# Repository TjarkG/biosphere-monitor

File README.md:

# Getting started with the Biosphere monitor command line tool

Get the repository and all its dependencies by running
`/bin/bash -c "$(curl -fsSL  https://raw.githubusercontent.com/TjarkG/biosphere-monitor/main/Shell/install.sh)"`

The Command line interface is started with `./biosphere`,
followed by a Port number (e.g. `/dev/ttyUSB0`) and optional arguments,
which can occur in any order, listed below:

* -h    show this help message
* -r    show current reading in Command line Output
* -rm   current output in machine-readable formate
* -s    show all saved readings. use pipes to save to a file
* -sc   same as -s, but with progress Updates on the Terminal. Use it to see the progress while piping
* -f    synchronize time
* -i    set measurement intervall in s, use -i? to get current intervall
* -t    run self test
* -ct   set current ambient Temperature(°C), used for Offset Calibration
* -delete delete Flash
* -gh   get current ADC reading of external input
* -ltn  set light on time, use -ltn? to get current setting
* -ltf  set light off time, use -ltf? to get current setting
* -lt   set light threshold, 0 for no threshold, use -lt? to get current setting

After cloning, generate makefiles with cmake:
```
mkdir cmake-build-debug
cd cmake-build-debug
cmake ..
```
and Compile the different programs:

* Command Line Tool: `make biosphere && ./biosphere /dev/ttyUSB0 -r`
* Graphical Configurator: `make bioGui`
* Microcontroller: `make Microcontroller.elf`

Check your data for Gaps with
`gawk -f Shell/gaps.awk gap=60 Documentation/Sample_Output.csv`
(gap is the intervall in s, each following argument is a Path to File to be checkt)

And convert it to an Excel Spreadsheet with
`soffice --convert-to xlsx --outdir ~/Dokumente/VS_Code/biosphere-monitor/Documentation Documentation/Sample_Output.csv --infilter=CSV:44,34,UTF8,true,3/10/4/10`

Complete Documentation (in German) can be found in /Documentation/Manual.pdf

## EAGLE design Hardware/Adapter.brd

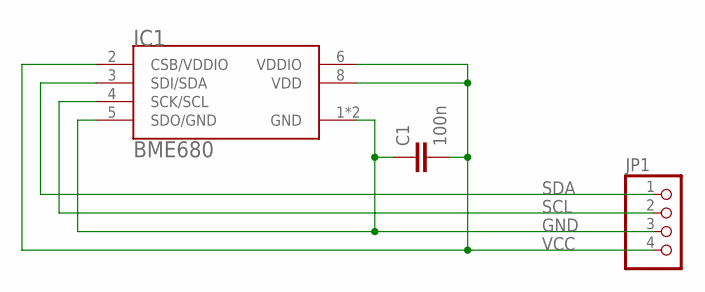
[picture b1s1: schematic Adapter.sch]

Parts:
C1: 100n; C0805
IC1: BME680; LGA8
JP1: PINHD-1X4; 1X04

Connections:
GND: C1.1, IC1.1 (GND), IC1.5 (SDO/GND), IC1.7 (GND), JP1.3
SCL: IC1.4 (SCK/SCL), JP1.2
SDA: IC1.3 (SDI/SDA), JP1.1
VCC: C1.2, IC1.2 (CSB/VDDIO), IC1.6 (VDDIO), IC1.8 (VDD), JP1.4

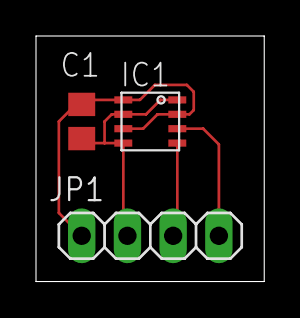
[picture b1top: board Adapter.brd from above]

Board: 2 copper layers, 12.7 x 13.6 mm, 3 parts (0 on the bottom side), 4 nets.

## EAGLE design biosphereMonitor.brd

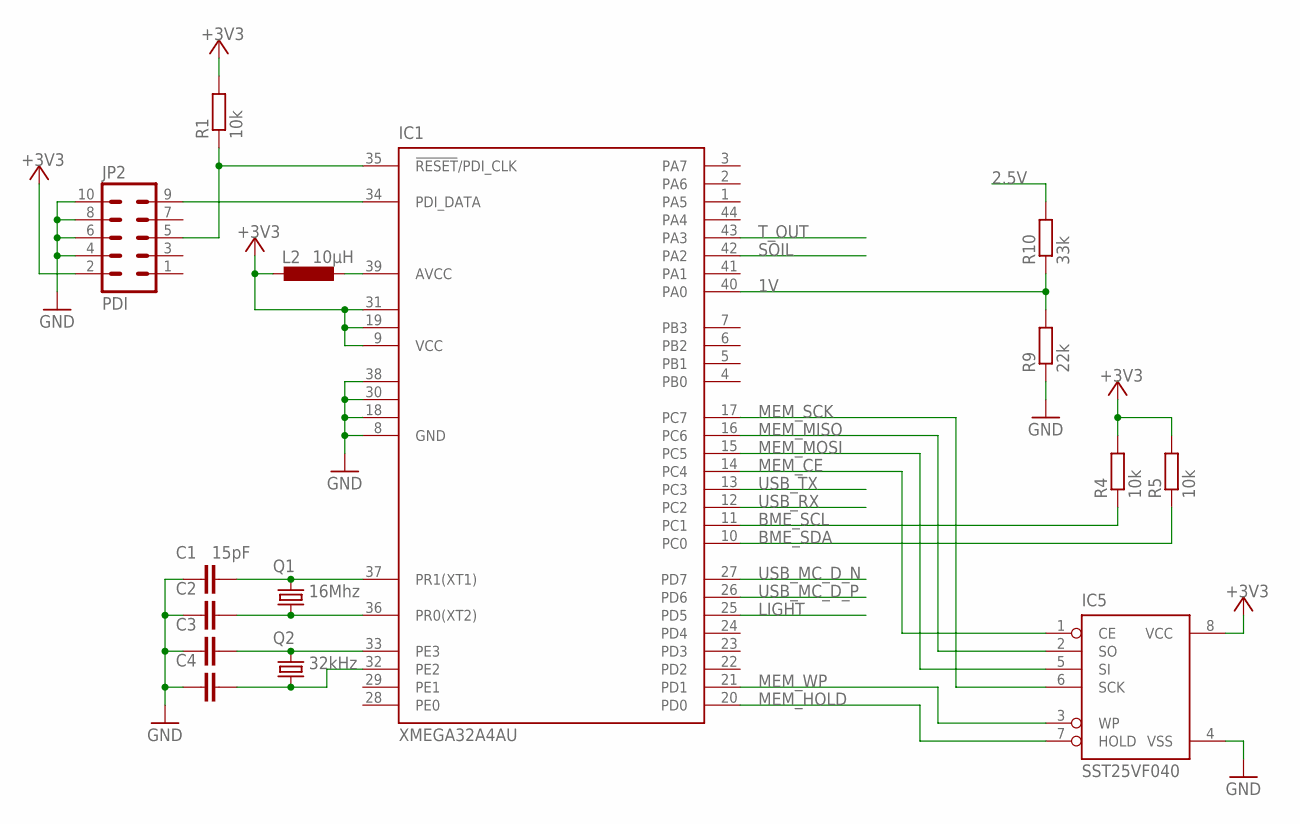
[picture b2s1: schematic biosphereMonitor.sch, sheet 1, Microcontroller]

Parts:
C1, C2, C3, C4: 15pF; C0805
IC1: XMEGA32A4AU; TQFP44
IC5: SST25VF040; SO08-208
JP2: PDI; ML10L
L2: 10µH; L2012C
Q1: 16Mhz; SM49
Q2: 32kHz; MS1V
R1, R4, R5: 10k; R0805
R9: 22k; R0805
R10: 33k; R0805

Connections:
1V: IC1.40 (PA0), R9.2, R10.1
2.5V: R10.2; also elsewhere on the board
+3V3: IC1.9 (VCC), IC1.19 (VCC1), IC1.31 (VCC2), IC5.8 (VCC), JP2.2, L2.1, R1.2, R4.2, R5.2; also elsewhere on the board
AVCC: IC1.39 (AVCC), L2.2
BME_SCL: IC1.11 (PC1), R4.1; also elsewhere on the board
BME_SDA: IC1.10 (PC0), R5.1; also elsewhere on the board
GND: C1.1, C2.1, C3.1, C4.1, IC1.8 (GND), IC1.18 (GND1), IC1.30 (GND2), IC1.38 (GND3), IC5.4 (VSS), JP2.4, JP2.6, JP2.8, JP2.10, R9.1; also elsewhere on the board
LIGHT: IC1.25 (PD5); also elsewhere on the board
MEM_CE: IC1.14 (PC4), IC5.1 (CE)
MEM_HOLD: IC1.20 (PD0), IC5.7 (HOLD)
MEM_MISO: IC1.16 (PC6), IC5.2 (SO)
MEM_MOSI: IC1.15 (PC5), IC5.5 (SI)
MEM_SCK: IC1.17 (PC7), IC5.6 (SCK)
MEM_WP: IC1.21 (PD1), IC5.3 (WP)
unnamed: IC1.35 (!RESET!/PDI_CLK), JP2.5, R1.1
unnamed: IC1.34 (PDI_DATA), JP2.9
unnamed: C1.2, IC1.37 (PR1(XT1)), Q1.2
unnamed: C2.2, IC1.36 (PR0(XT2)), Q1.1
unnamed: C3.2, IC1.33 (PE3), Q2.Q1 (1)
unnamed: C4.2, IC1.32 (PE2), Q2.Q2 (2)
SOIL: IC1.42 (PA2); also elsewhere on the board
T_OUT: IC1.43 (PA3); also elsewhere on the board
USB_MC_D_N: IC1.27 (PD7); also elsewhere on the board
USB_MC_D_P: IC1.26 (PD6); also elsewhere on the board

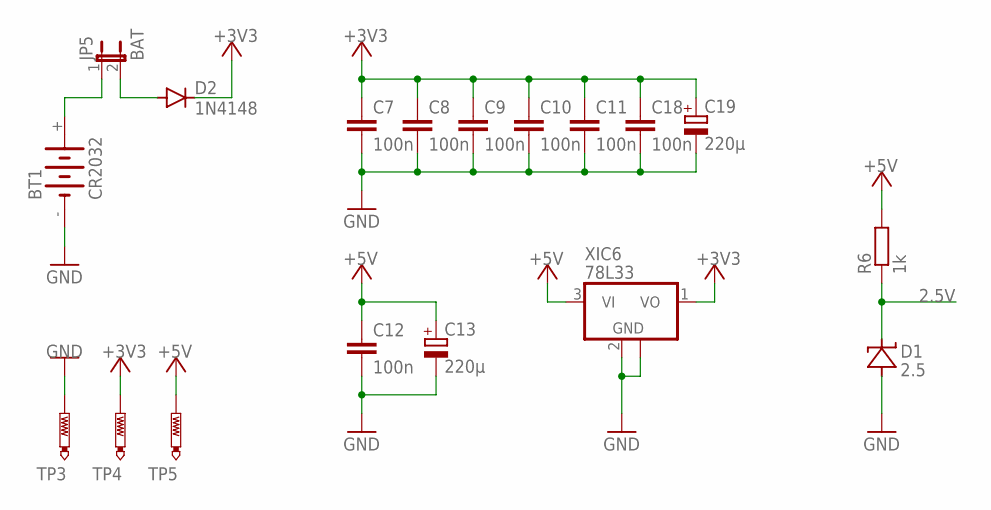
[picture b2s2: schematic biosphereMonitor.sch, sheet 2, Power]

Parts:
BT1: CR2032
C7, C8, C9, C10, C11, C12, C18: 100n; C0805
C13, C19: 220µ; PANASONIC_G
D1: 2.5; SOT23
D2: 1N4148; MINIMELF
JP5: BAT; JP1
R6: 1k; R0805
TP3, TP4, TP5: PTR1B2,54; B2,54
XIC6: 78L33; SOT89

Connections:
2.5V: D1.1 (C), R6.1; also elsewhere on the board
+3V3: C7.2, C8.2, C9.2, C10.2, C11.2, C18.2, C19.+, D2.C, TP4.TP, XIC6.1 (VO); also elsewhere on the board
+5V: C12.2, C13.+, R6.2, TP5.TP, XIC6.3 (VI); also elsewhere on the board
GND: BT1.-, C7.1, C8.1, C9.1, C10.1, C11.1, C12.1, C13.-, C18.1, C19.-, D1.2 (A), TP3.TP, XIC6.2 (GND), XIC6.2@1 (GND); also elsewhere on the board
unnamed: BT1.+, JP5.1
unnamed: D2.A, JP5.2

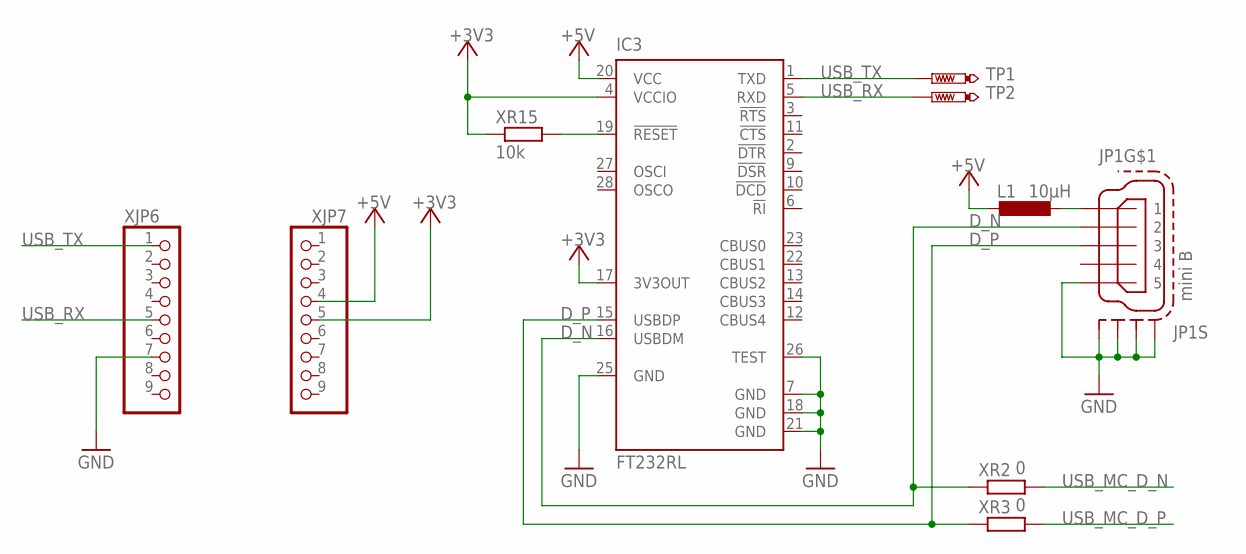
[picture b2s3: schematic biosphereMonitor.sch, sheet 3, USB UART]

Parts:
IC3: FT232RL; SSOP28
JP1: mini B; 32005-301
L1: 10µH; L2012C
TP1, TP2: PTR1B2,54; B2,54
XJP6, XJP7: PINHD-1X9; 1X09
XR2, XR3: 0; R0805
XR15: 10k; R0805

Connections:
+3V3: IC3.4 (VCCIO), IC3.17 (3V3OUT), XJP7.5, XR15.1; also elsewhere on the board
+5V: IC3.20 (VCC), L1.1, XJP7.4; also elsewhere on the board
D_N: IC3.16 (USBDM), JP1.2, XR2.1
D_P: IC3.15 (USBDP), JP1.3, XR3.1
GND: IC3.7 (GND), IC3.18 (GND), IC3.21 (GND), IC3.25 (GND), IC3.26 (TEST), JP1.5, JP1.M1 (S1), JP1.M2 (S2), JP1.M3 (S3), JP1.M4 (S4), XJP6.7; also elsewhere on the board
unnamed: JP1.1, L1.2
unnamed: IC3.19 (!RESET), XR15.2
USB_MC_D_N: XR2.2; also elsewhere on the board
USB_MC_D_P: XR3.2; also elsewhere on the board

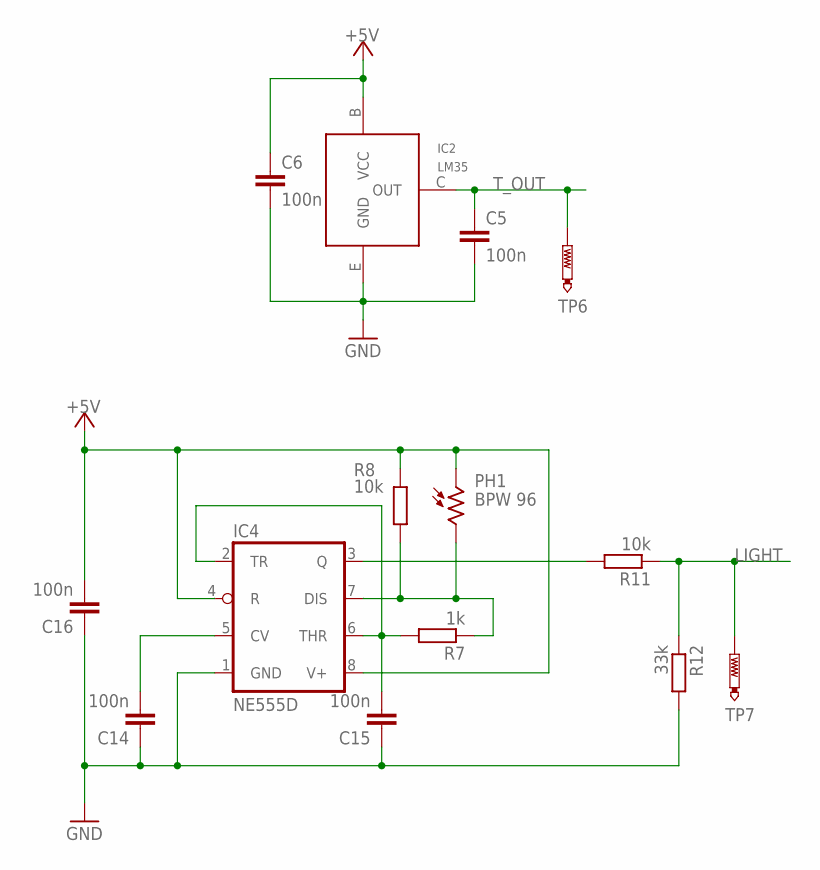
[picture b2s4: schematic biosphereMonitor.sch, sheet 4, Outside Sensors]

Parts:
C5, C6, C14, C15, C16: 100n; C0805
IC2: LM35; TO92-BCE
IC4: NE555D; SO08
PH1: BPW 96; T0-46-A10XX
R7: 1k; R0805
R8, R11: 10k; R0805
R12: 33k; R0805
TP6, TP7: PTR1B2,54; B2,54

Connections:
+5V: C6.2, C16.1, IC2.B (VCC), IC4.4 (R), IC4.8 (V+), PH1.1, R8.1; also elsewhere on the board
GND: C5.1, C6.1, C14.2, C15.2, C16.2, IC2.E (GND), IC4.1 (GND), R12.2; also elsewhere on the board
LIGHT: R11.1, R12.1, TP7.TP; also elsewhere on the board
unnamed: IC4.7 (DIS), PH1.2, R7.1, R8.2
unnamed: C14.1, IC4.5 (CV)
unnamed: C15.1, IC4.2 (TR), IC4.6 (THR), R7.2
unnamed: IC4.3 (Q), R11.2
T_OUT: C5.2, IC2.C (OUT), TP6.TP; also elsewhere on the board

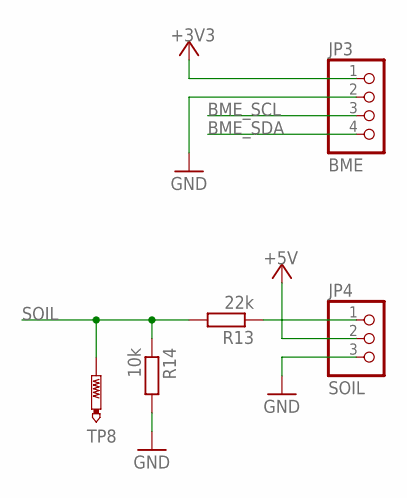
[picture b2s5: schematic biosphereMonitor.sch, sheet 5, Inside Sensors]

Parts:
JP3: BME; 1X04
JP4: SOIL; 1X03
R13: 22k; R0805
R14: 10k; R0805
TP8: PTR1B2,54; B2,54

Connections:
+3V3: JP3.1; also elsewhere on the board
+5V: JP4.2; also elsewhere on the board
BME_SCL: JP3.3; also elsewhere on the board
BME_SDA: JP3.4; also elsewhere on the board
GND: JP3.2, JP4.3, R14.2; also elsewhere on the board
unnamed: JP4.1, R13.1
SOIL: R13.2, R14.1, TP8.TP; also elsewhere on the board

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
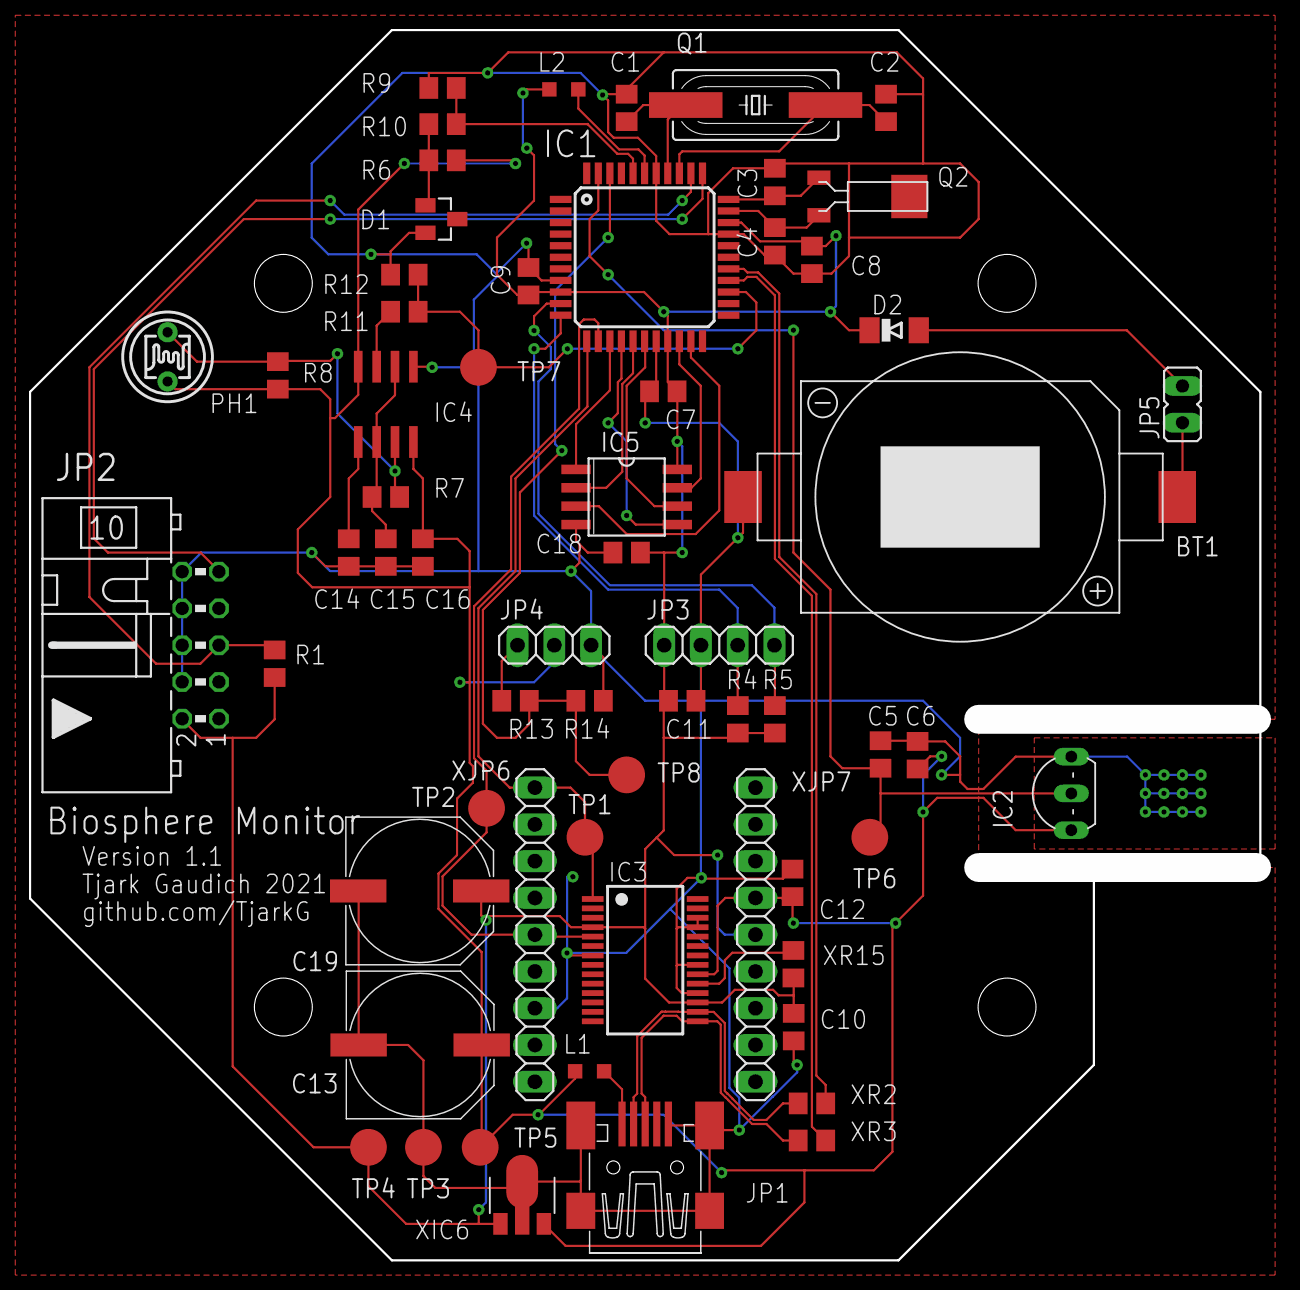
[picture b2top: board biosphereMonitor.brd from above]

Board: 2 copper layers, 83.8 x 83.2 mm, 62 parts (0 on the bottom side), 38 nets.

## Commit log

2021-08-26 Added basic Readme and gitignore
2021-08-26 added blink workflow test
2021-08-28 added UART and RTC
2021-08-28 added Struct for readings
2021-08-29 added Intervall and ADC Reading
2021-08-30 fixed backslash warning
2021-08-30 added instruction set for command line tool
2021-08-30 defined function set for command line tool, added iaq to results
2021-08-30 added using of arguments
2021-08-30 added reading printout
2021-08-30 changed light type
2021-08-30 moved readings struct to header file
2021-08-30 UART ISr Comment
2021-08-30 added Comment
2021-08-30 finished Outside Temperature getter
2021-08-30 chnaged Clock to 16Mhz extern
2021-08-30 tried to add sleep mode
2021-08-30 centralized Pin Direction assigment
2021-08-31 added checkin for Power bevor leaving RTC ISR
2021-08-31 added CSV generation
2021-08-31 switching TX off in Standby to save power
2021-08-31 added standard interface to MC
2021-08-31 added COM Port support
2021-09-01 added EOF affter readings ar transmitted
2021-09-01 changed Helpfile Source
2021-09-01 added Help Formating
2021-09-01 changed Baud Rate to 115200
2021-09-01 added feedback for each Option
2021-09-01 tiedied up MC Code
2021-09-01 changed definition to match code
2021-09-02 formated tty.h
2021-09-02 added comments
2021-09-02 added function for geter readings
2021-09-02 tiedied up sourcecode
2021-09-02 formated printReading
2021-09-04 added cost estimate
2021-09-04 added bmp280 temperatur readout
2021-09-04 added pressure output
2021-09-04 made Air Humidity Optional
2021-09-04 added BME to Selftest
2021-09-06 fixed Sensor readout not working
2021-09-06 added power supply to Cost Estimate
2021-09-06 added basic offset correction
2021-09-07 new readings
2021-09-07 changed reset procedure
2021-09-07 added schematic
2021-09-07 added Outside Temperatur Calibration
2021-09-08 moved offset corection into function
2021-09-08 improved inside Temperature Sensor reading
2021-09-09 changed inOff type to int
2021-09-09 added adc input for humidity and illuminance
2021-09-09 added error managment to getReading function
2021-09-12 Defined Board Shape
2021-09-12 changed Sorting from Linsort to Quicksort
2021-09-13 Sorted Project in Directorys
2021-09-13 changed the new commands to inline code
2021-09-13 added file opening for calculator
2021-09-13 added Reading of csv in structs
2021-09-13 added Calculator Command
2021-09-14 added gaussian elimination
2021-09-15 eliminat now dircetly accepts array of points
2021-09-15 messured different Brightneses
2021-09-16 added light sensor to schematic
2021-09-17 formating
2021-09-17 added extrenal Voltage reference
2021-09-17 added reference in schematic
2021-09-17 calibration now takes float temperatures
2021-09-18 added messurments
2021-09-19 added additional set of messurments with frequency
2021-09-19 added exponetial aproximation
2021-09-20 added exponential function struct
2021-09-20 added calculation of exponential functions
2021-09-20 increased accuracy
2021-09-20 put messurments in in.csv
2021-09-20 added guessing of better function
2021-09-21 started implementign binary aproximation
2021-09-21 changed light Sensor to frequency Messurment
2021-09-22 added lux messurment
2021-09-22 added humidity conversion to percent and completed schematic
2021-09-22 placed Parts
2021-09-22 routed board
2021-09-24 added PCB options and cam file
2021-09-24 added option for external ftdi board
2021-09-24 changed some footprints
2021-09-25 filled groundplane
2021-09-25 added basic Flash functions
2021-09-25 added saving of periodic readings
2021-09-26 completed saving of readings to flash
2021-09-26 added BME 680 Temperature readout
2021-09-26 added other BME functions (gas resistence not working yet)
2021-09-27 toke one night of messurments
2021-09-27 changed decimal Seperator in Output File to Comma
2021-10-08 optimized layout optics
2021-10-11 chnaged MC to XMEGA32A4U
2021-10-11 removed manual setting of soil sensor state
2021-10-11 made the microcontroller start without BME attatched
2021-10-11 removed unnecesary parts
2021-10-12 moved components away from screws
2021-10-12 added vertification to time syncronization
2021-10-12 improved selftest
2021-10-12 played around with 3d models
2021-10-12 improved error handling if a wrong com port is provided
2021-10-12 changed rx with tx
2021-10-13 fixed inside temperature caluclation for csv output
2021-10-13 changed temperature source for pressure messurment
2021-10-14 added correction factor for BMX280
2021-10-14 reverted last commit
2021-10-18 added status bar when saving readings
2021-10-19 added errrorcode output
2021-10-21 added Flash read/write check
2021-10-23 bits read from Sensor are now in the right order
2021-10-23 tiedied up Temperatur and Pressur Code
2021-10-23 added BME 280 Humidity Messurment
2021-10-24 improved readout for BME 680
2021-10-25 moved PCB files into folder
2021-10-25 made iaq messurmetn work
2021-10-25 adjusted Light Messurment for PCBA in an Enclousur
2021-10-27 added flash errase check (untested)
2021-10-28 added make option for 16A4U
2021-10-29 added defines for Windows version
2021-10-30 removed offset from SoilHum function
2021-10-30 added half working COM Port access
2021-10-31 added further addoption to windows, everything except for saving works
2021-10-31 added dely bevor answer is send because windwos is wierd
2021-11-03 added final function for lux messurment
2021-11-03 updated cost estimate
2021-11-18 refactoring
2021-11-22 deleted old executable
2021-11-27 added Manual Draft
2021-11-28 continued writing Manual
2021-11-28 sortet Files
2021-11-28 stopped including .vscode
2021-11-28 updatet README
2021-11-28 added 3d models
2021-11-28 added B/D to Bibliografie
2021-11-28 made Makefile clearer
2021-11-29 added refences to datasheets
2021-11-30 added µC Pin describtion
2021-12-08 moved status messanges to stderr
2021-12-08 moved save output to stdout
2021-12-08 removed remains of saving directly to file
2021-12-08 stopped commiting compiled output
2021-12-08 started adding explination for light Sensor
2021-12-08 seperated saving in commenting and non commenting mode
2021-12-08 removed distinction in date formate between Windows and Unix
2021-12-08 replaced calc by explanation in Manual
2021-12-08 added links to relevant files
2021-12-09 put pin describtionin table
2021-12-10 started writing software section
2021-12-11 added unknown argument warning
2021-12-11 produced new sample output
2021-12-11 completed instalation guide
2021-12-12 added edgecase for reading out right after deleting flash
2021-12-12 adjusted buffer sizes
2021-12-12 simplified break condition check
2021-12-12 addedexlanation for last commit
2021-12-12 added instalation script
2021-12-12 added support for different package managers
2021-12-12 removed sudo from apk to work in iSH
2021-12-12 added explaination of installation script
2021-12-12 added machine readable -r
2021-12-12 started writing kiosk mode script
2021-12-13 completed kiosk script
2021-12-14 made ctrl+c restore the courser too
2021-12-14 fixed tab jumping for 3 digit iluminance
2021-12-14 added scripts to manual
2021-12-14 toke care of most hbox warnings
2021-12-16 added script to automat result distribution
2021-12-19 made it possible to have blanks in names
2021-12-19 removed debug prints
2021-12-20 added option to get ADC reading of external sensor
2021-12-20 fixed formating of -gh option
2021-12-20 kiosk.sh now works out of every directory
2021-12-20 removed unnecessary echo
2021-12-21 removed compilation from bioPi.sh
2021-12-21 added transfer function for soil humidity
2022-01-08 made comment more acurate
2022-01-09 added Rust implementation of PC Software
2022-01-09 moved sync into function
2022-01-15 started writing gapfinder
2022-01-15 completed gap detection
2022-01-15 filed gaps in sampel
2022-01-15 reformated Interface Standard
2022-01-18 added makefile for PC Software
2022-01-18 added warning if one Data set is ditributed twice in a row
2022-01-18 added note to gap finder to readme
2022-01-19 Added Gap Checking to mail Script
2022-01-19 changed ending of biopi to .awk
2022-01-20 Added Missing Brackets
2022-01-20 added command to convert to xlsx and example document
2022-01-20 added xlsx attachment to bioPi mails
2022-01-21 integrated date conversion into awk to reduce number of child processes
2022-01-21 changed from awk to gawk to use switch
2022-01-21 temporarly removed to xlsx conversion till dependencys are installed on server
2022-01-22 added libreoffice dependecy
2022-01-22 added generating Data directory on Installation
2022-01-25 Removed conversion because Java doesnt work
2022-03-06 made saving and chaning intervall portable
2022-03-06 now requiring precise syntax for arguments
2022-03-06 put all arguments into functions
2022-03-06 moved readingIt
2022-03-06 seperated source and header files properly
2022-03-06 updated documentation
2022-03-06 unified header and sorted includes
2022-03-06 copyed Gui from gui tests
2022-03-06 connected synctime
2022-03-06 added intervall window
2022-03-06 completed intervall setting
2022-03-06 added live values
2022-03-06 displayed missing statistics
2022-03-06 corected needed malloc size (reading is bigger on x86)
2022-03-06 fixed lnCnt of by one
2022-03-06 implemented selftest
2022-03-07 now detects when no biosphäre is connected
2022-03-07 added source selection
2022-03-07 added install option to make
2022-03-07 added Desktop Icon
2022-03-08 added saving to default path
2022-03-09 fixed wrong formular for rh soil
2022-03-09 changed default return to 0
2022-03-10 added mailutils dependency
2022-03-11 readded exiting when Port cant be opend
2022-03-11 added ssmtp dependency
2022-03-11 added missing includes
2022-03-11 put bme code in a proper file
2022-03-11 removed nonworking iaq code
2022-03-11 unified mc define and removed and unnecessary one
2022-03-11 added read timeout
2022-03-11 moved setting isConnected behind timeout detection
2022-03-11 seperated gui and cli folders
2022-03-11 added redirects for microcontroller make targets
2022-03-21 stoped assuming file locations
2022-03-21 fixed mailserver
2022-03-21 re added file conversion
2022-03-22 added note for transmitting local data
2022-04-19 corrected makefile
2022-04-19 repaired makefile even more
2022-04-20 fixed typo
2022-08-13 improved makefile
2022-08-13 fixed bugs
2022-08-13 improved readability
2022-08-14 copyed improved makefile from SpiController
2022-08-14 added reading into array
2022-08-14 optimization
2022-08-14 removed unneded defines
2022-08-15 started intro pressentation
2022-08-15 improved scaling and pressure resolution
2022-08-15 unified oversampling
2022-08-15 corrected comments
2022-08-15 increased clock speeds
2022-08-15 improved memory layout
2022-08-16 fixed setTime hanging
2022-08-16 fixed selftest with new pressure range
2022-08-16 added save as
2022-08-16 added datasheet link
2022-08-16 fixed makefile installation
2022-08-18 fixed broken flash code
2022-08-18 removed executables from repo
2022-08-18 removed non working converter code
2022-08-28 fixed uncomplet deletion issue
2022-10-30 added lamp functions to microcontroller
2022-10-31 moved help to cli
2022-10-31 added light controlls to cli
2022-10-31 converted cli to c++
2022-10-31 fixed formating and strncmp lengths
2022-10-31 noticed a day had more than 2¹⁶ Seconds
2022-12-19 simpliefied help function with fileString
2022-12-20 fixed Typos
2022-12-20 fixed warnings, replaced nonstandard functions
2023-03-22 added PDF schematic
2023-03-25 Switched Microcontroller to use CMake
2023-03-25 Moved the Whole Project to CMake
2023-03-25 basic c to c++ transformation
2023-03-25 fixed reading flash returning garbage & getID hanging
2023-03-25 updated documentation and scripts with new paths
